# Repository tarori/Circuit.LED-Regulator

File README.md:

Discrete 3-terminal regulator
* Designed for DAC supply
* 780x compatible
* Output voltage 3.3V ~ 12V
* Low impedance even at high frequency
* Use LED as low noise reference

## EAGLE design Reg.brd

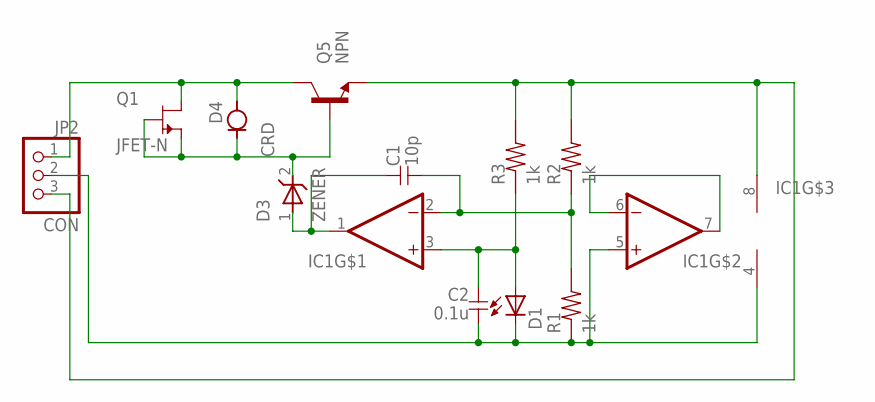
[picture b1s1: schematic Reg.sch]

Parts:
C1: 10p; 1608
C2: 0.1u; 2012
D1: LED-SMD2012; D2012
D3: ZENER; SOD123
D4: CRD; SOD123
IC1: OPA-2-SOP; SOP8
JP2: CON; 1X03
Q1: JFET-N; SC59
Q5: NPN; TO126-2
R1, R2, R3: 1k; 1608

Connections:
GND1: C2.2, D1.K, IC1.4 (V-), IC1.5 (+IN), JP2.2, R1.1
IN1: D4.1 (A), JP2.1, Q1.2 (D), Q5.2 (C)
unnamed: C2.1, D1.A, IC1.3 (+IN), R3.1
unnamed: D3.2 (C), D4.2 (K), Q1.1 (S), Q1.3 (G), Q5.3 (B)
unnamed: C1.2, IC1.2 (-IN), R1.2, R2.1
unnamed: C1.1, D3.1 (A), IC1.1 (OUT)
unnamed: IC1.6 (-IN), IC1.7 (OUT)
OUT1: IC1.8 (V+), JP2.3, Q5.1 (E), R2.2, R3.2

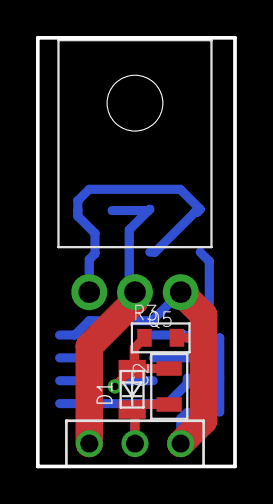
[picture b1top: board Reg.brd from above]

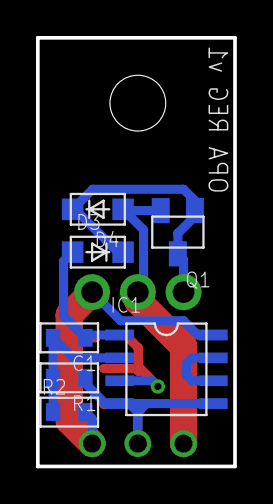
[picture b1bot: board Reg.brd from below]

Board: 2 copper layers, 11.0 x 23.8 mm, 12 parts (7 on the bottom side), 8 nets.

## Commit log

2020-06-24 ver1
2020-06-24 こんな感じ
2020-06-24 帰還ループの改善
2020-07-03 チップオンリーも
2020-07-03 Vカット
2020-07-03 Add readme
2020-07-16 ダーリントン、二段増幅を追加
2021-03-26 幅を小さくした
2021-03-26 V-CUT
2022-12-19 シンプルisBest
2022-12-19 ダーリントン
2022-12-19 LDO ver
2022-12-19 OPA ver
